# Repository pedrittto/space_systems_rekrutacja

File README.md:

# Current Measurement Module & Step Down Converter

## Autor: Piotr Radziej

## 1.Moduł pomiaru prądu 50A / 24V
Zaprojektowany układ typu **High-Side** oparty na precyzyjnym wzmacniaczu pomiarowym.

* **Specyfikacja:**
    * Zakres prądowy: do 50A (szczytowo 65A).
    * Wyjście: liniowe 0-3.3V, gotowe pod ADC.
    * Układ: **INA290A3** (Gain 100 V/V).
    * Bocznik: 0.5 mΩ, obudowa 2512 (niski dryft termiczny).
* **Cechy projektu:**
    * Zastosowanie połączeń Kelvina dla maksymalnej precyzji.
    * Filtr wyjściowy RC.

## 2.Przetwornica Step-Down 5V / 3A
Projekt synchronicznej przetwornicy Buck opartej na układzie **AP63300**.

* **Specyfikacja:**
    * Wejście: 24V nominalnie (max 32V).
    * Wyjście: 5V / 3A ciągłego obciążenia.
    * Częstotliwość: 500 kHz (Spread Spectrum EMI reduction).
* **Cechy projektu:**
    * Minimalizacja pętli **Hot Loop** (kondensator C1 tuż przy pinach VIN/GND).
    * Zredukowany poligon węzła SW dla ograniczenia emisji EMI.

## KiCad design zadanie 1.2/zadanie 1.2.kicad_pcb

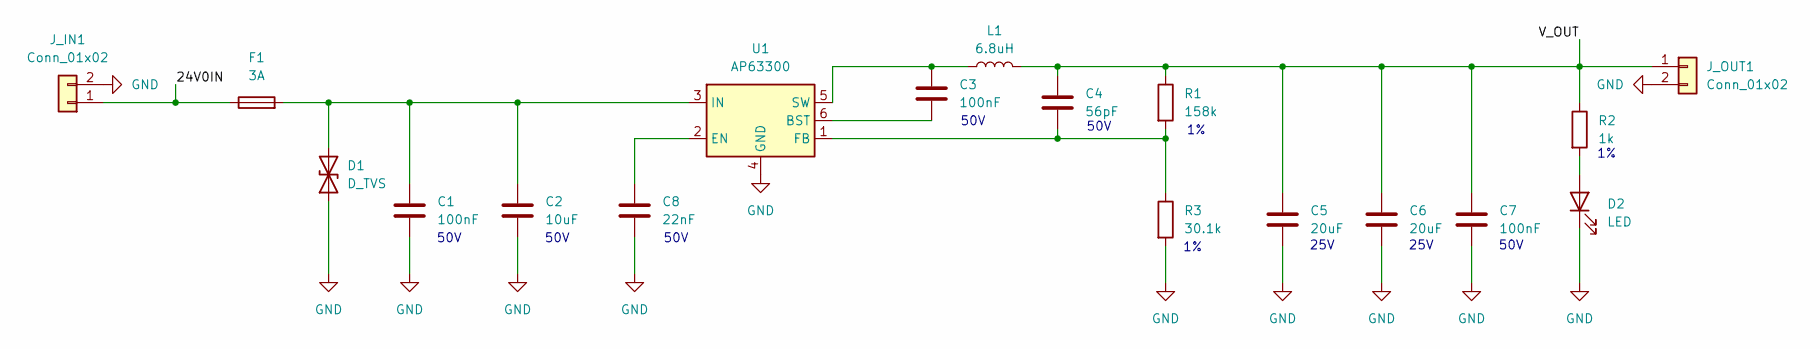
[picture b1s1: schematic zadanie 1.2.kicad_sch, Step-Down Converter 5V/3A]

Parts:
C1, C3, C7: 100nF; C_0603_1608Metric
C2: 10uF; C_1210_3225Metric
C4: 56pF; C_0603_1608Metric
C5, C6: 20uF; C_1206_3216Metric
C8: 22nF; C_0603_1608Metric
D1: D_TVS; D_SMB
D2: LED; LED_0805_2012Metric
F1: 3A; Fuse_1206_3216Metric
J_IN1: Conn_01x02; TerminalBlock_Phoenix_MKDS-1,5-2_1x02_P5.00mm_Horizontal
J_OUT1: Conn_01x02; TerminalBlock_Phoenix_MKDS-1,5-2_1x02_P5.00mm_Horizontal
L1: 6.8uH; L_7.3x7.3_H4.5
R1: 158k; R_0603_1608Metric
R2: 1k; R_0603_1608Metric
R3: 30.1k; R_0603_1608Metric
U1: AP63300; TSOT-23-6

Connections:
/24V0IN: F1.1, J_IN1.1
/V_OUT: C4.1, C5.1, C6.1, C7.1, J_OUT1.1, L1.2, R1.1, R2.1
GND: C1.2, C2.2, C5.2, C6.2, C7.2, C8.2, D1.1 (A1), D2.1 (K), J_IN1.2, J_OUT1.2, R3.2, U1.4 (GND)
unnamed: C1.1, C2.1, D1.2 (A2), F1.2, U1.3 (IN)
unnamed: D2.2 (A), R2.2
unnamed: C3.2, U1.6 (BST)
unnamed: C8.1, U1.2 (EN)
unnamed: C4.2, R1.2, R3.1, U1.1 (FB)
unnamed: C3.1, L1.1, U1.5 (SW)

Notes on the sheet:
50V
25V

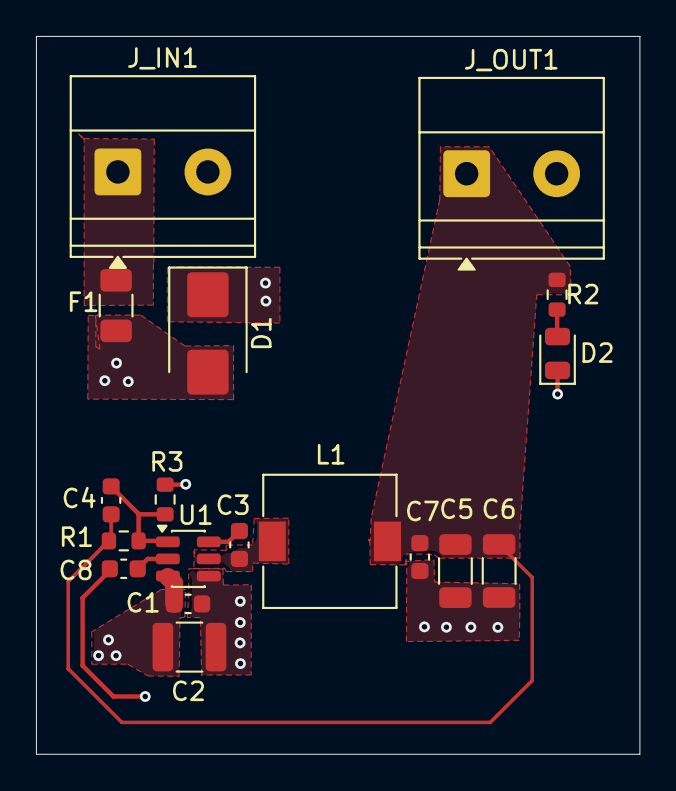
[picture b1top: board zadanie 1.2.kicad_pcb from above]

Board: 2 copper layers, 33.5 x 39.9 mm, 18 parts (0 on the bottom side), 9 nets.

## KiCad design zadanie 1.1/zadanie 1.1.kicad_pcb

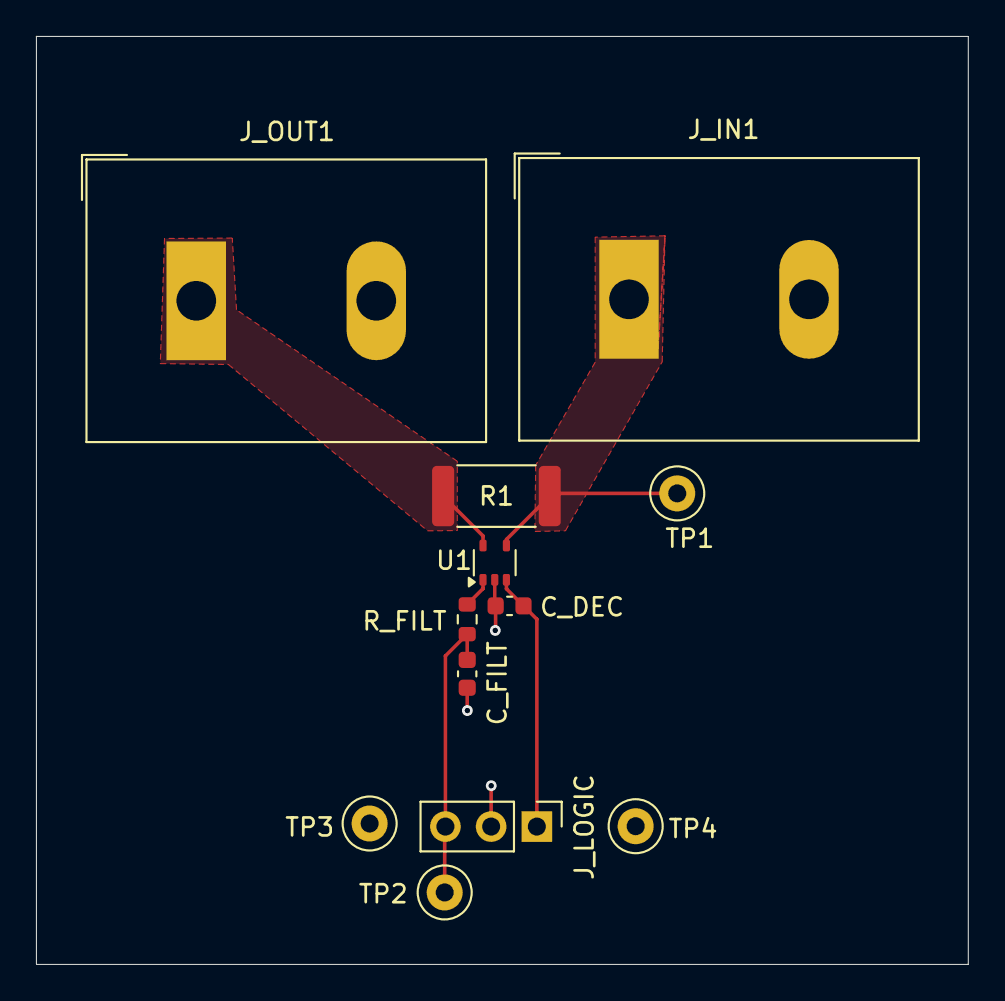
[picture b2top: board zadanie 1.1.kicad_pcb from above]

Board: 2 copper layers, 51.8 x 51.6 mm, 12 parts (0 on the bottom side), 6 nets.

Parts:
C_DEC: 100nF; C_0603_1608Metric
C_FILT: 10nF; C_0603_1608Metric
J_IN1: Screw_Terminal_01x02; TerminalBlock_Dinkle_DT-55-B01X-02_P10.00mm
J_LOGIC: Conn_01x03_Pin; PinHeader_1x03_P2.54mm_Vertical
J_OUT1: Screw_Terminal_01x02; TerminalBlock_Dinkle_DT-55-B01X-02_P10.00mm
R1: 0.5 mohm; R_2512_6332Metric
R_FILT: 1k; R_0603_1608Metric
TP1, TP2, TP3, TP4: TestPoint; TestPoint_Loop_D2.50mm_Drill1.0mm
U1: INA290A3xDCK; SOT-353_SC-70-5

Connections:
+3V3: C_DEC.1, J_LOGIC.1, U1.3 (V+)
/ADC_OUT: C_FILT.1, J_LOGIC.3, R_FILT.2, TP2.1
/LOAD_24V: J_OUT1.1, R1.1, U1.5 (-)
/SENSE+: J_IN1.1, R1.2, TP1.1, U1.4 (+)
GND: C_DEC.2, C_FILT.2, J_IN1.2, J_LOGIC.2, J_OUT1.2, TP3.1, TP4.1, U1.2 (GND)
unnamed: R_FILT.1, U1.1

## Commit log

2026-03-22 Update README with project details for recruitment tasks
    Added detailed project descriptions and specifications for recruitment tasks in electronics.
2026-04-27 Trigger new deploy
    Updated project titles and removed section on connector selection.
